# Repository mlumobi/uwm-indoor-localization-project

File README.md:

# UWB TDoA Real-time Localization

An EC601 course project to build and evaluate an indoor location system for tagged objects using ultra wideband (UWB) radio and uplink time difference of arrival (TDoA).

This is a one-person project. Mingjin Lu is responsible for hardware integration, firmware, localization software, evaluation, and documentation, with AI assistance.

**Status:** Proposal stage. This repository currently contains the project proposal and reference documents. Firmware, localization software, and measured performance results are not yet included. Accuracy, update rate, and reliability values below are proposed targets, not demonstrated capabilities.

## Five Ws and How

| Question | Project definition |
| --- | --- |
| **What** | An indoor monitoring prototype for tagged robots and vehicles, with a live 2D map, distinct tag IDs, position freshness and validity indicators, configurable safety zones, alerts for non-permitted zone entry, abnormal motion and prolonged signal loss, and recorded-movement replay. The physical prototype targets two tags and three anchors; additional tags may be simulated and clearly labeled. |
| **Who** | The primary target user is a warehouse or factory safety manager overseeing a shared workspace with vehicles, people, robots, and machinery. A robotics engineer also needs to monitor a robot without integrating with its onboard navigation software. Mingjin Lu is the sole developer, with AI assistance; user needs and interface usefulness still require interviews. |
| **Why** | Help the user see where tagged robots or vehicles are, recognize restricted-zone entries and unreliable tracking information, and review past movement. Evaluate these monitoring functions against measured ground truth and scripted scenarios; improved workplace safety and attack detection are not established outcomes. |
| **When** | The Sprint 1 two-week demo will show a labeled Python simulation, purchase and delivery progress, and the hardware implementation plan. After parts arrive, bring up the hardware, validate anchor clock correction, demonstrate one physical tag, then add the second tag and evaluate tracking and alerts. |
| **Where** | The intended application is a shared warehouse or factory workspace. Initial physical evaluation will use a controlled, surveyed indoor test area with known tag height and mapped zone boundaries; assembly and electrical checks are planned at RASTIC. Industrial deployment requires separate validation. |
| **How** | Start with simulated UWB arrival timestamps to test localization, map display, alerts, and replay. For hardware, use DWM3000 modules with XIAO ESP32C3 controllers: tags broadcast uplink blinks, three anchors record receive timestamps, and a computer corrects anchor clocks using periodic anchor-to-anchor UWB two-way exchanges, calculates TDoA positions, and applies the monitoring rules. Wi-Fi forwards records. Retain position and alert logs, compare accuracy and delay with ground truth, and use tag-to-anchor TWR as the fallback if clock correction fails its timing criteria. |

## Planned demonstration

- Two tags and three fixed anchors, each using a DWM3000 UWB module with an ESP32 or another compatible microcontroller.
- A controlled 2D test area with surveyed anchor positions and known tag height.
- Wi-Fi forwarding of timestamp records to a central computer; Bluetooth remains an option to evaluate.
- A live map with tag IDs, position age, and invalid or stale states.
- Raw measurement logs and replayable evaluation results.

Qorvo lists the DWM3000 for TWR and TDoA tag or anchor use, with a customer-supplied MCU. The module does not integrate Bluetooth, so any Bluetooth connection must come from another component. These specifications support the proposed architecture but do not establish this prototype’s performance. [Qorvo DWM3000](https://www.qorvo.com/products/p/DWM3000)

## Localization architecture

```text
Two UWB tags
    │ UWB broadcasts with tag ID and sequence number
    v
Three fixed anchors
    │ Hardware arrival timestamps and receive diagnostics
    │ Wi-Fi backhaul
    v
Central computer
    Clock correction -> frame matching -> TDoA solver -> map and logs
```

In uplink TDoA, anchors observe the same tag transmission. Differences in its arrival times correspond to differences in path lengths. Anchor clock synchronization or correction is essential; Wi-Fi or Bluetooth transports the records and does not, by itself, establish the required UWB timing basis. The proposed records therefore contain **arrival timestamps**, rather than independently measured tag-to-anchor distances. [ESP32 and DWM3000 study](https://arxiv.org/html/2403.10194v1)

**Recommended first experiment:** Verify that the selected boards and driver can produce consistent, corrected timestamps before building the full interface. A published ESP32/DWM3000 system uses two-way ranging (TWR); it provides hardware precedent but does not validate my uplink TDoA design. TWR may serve as a hardware baseline or an explicitly labeled fallback. [ESP32 and DWM3000 study](https://arxiv.org/html/2403.10194v1)

Three anchors provide two independent time differences for a known-height 2D model. This is a minimal configuration with no extra measurement redundancy; it does not guarantee a unique or well-conditioned position. A fourth anchor is a recommended improvement if resources allow. Anchor placement and obstructed radio paths must be evaluated because both affect TDoA localization quality. [Sensor placement study](https://arxiv.org/abs/2204.04508)

## Proposed evaluation targets

These targets require confirmation after user interviews and the initial timing experiment.

| Measure | Proposed criterion |
| --- | --- |
| Static horizontal accuracy | Median error ≤0.30 m and 95th-percentile error ≤0.75 m across nine surveyed test positions. |
| Valid-position ratio | At least 95% of scheduled tag transmissions produce accepted positions, reported separately for each tag. |
| Tag transmission rate | Start at 10 Hz per tag and report the achieved valid-position update rate. |
| Stale-state detection | Mark a position stale within one second of the last accepted estimate. |
| Reproducibility | A reviewer can replay retained records and reproduce the reported metrics using the documentation. |

Calibration and evaluation data should be separated. Report missed transmissions, rejected estimates, per-position errors, and obstructed-path results. Human tracking, robot control, free-height 3D localization, and industrial deployment remain outside the initial demonstration.

## Development plan

1. Interview prospective users, confirm hardware and course dates, and test a paper map.
2. Verify board communication and anchor clock correction; create a clearly labeled recorded-data demo.
3. Demonstrate one live tag end to end, then evaluate the surveyed area.
4. Add the second tag and test identity, update behavior, and failure states.
5. Publish reproducible measurements and document failed criteria and limitations.

The proposal contains five user stories with acceptance criteria, an INVEST review, thin demo slices, and ranked assumptions with tests and pivot criteria. No feasibility test results are available yet.

## Repository contents

```text
README.md
proposal/
    UWB_Project_Proposal.docx
    UWB_Project_Proposal.pdf
ref/
    DWM3000 Data Sheet.pdf
    HID-whitepaper-UWB-guide-for-decision-makers.pdf
    qorvo-getting-back-to-basics-with-ultra-wideband-uwb-white-paper.pdf
```

- [Project proposal — Word](proposal/UWB_Project_Proposal.docx)
- [Project proposal — PDF](proposal/UWB_Project_Proposal.pdf)
- [DWM3000 data sheet](ref/DWM3000%20Data%20Sheet.pdf)
- [HID UWB whitepaper](ref/HID-whitepaper-UWB-guide-for-decision-makers.pdf)
- [Qorvo — Getting Back to Basics with Ultra-Wideband (UWB)](ref/qorvo-getting-back-to-basics-with-ultra-wideband-uwb-white-paper.pdf)

The HID whitepaper is retained as a background reference; it was not used as evidence in the current proposal. Setup and execution instructions will be added when runnable software is available.

## Sources and course guide

- [EC601_Sprint1](https://docs.google.com/presentation/d/1xGqi0pRQQJJB1kcCf-J-DX_ZKf9MRdXoSHOy6zalLVk/edit?slide=id.p1#slide=id.p1) — recurring reference for this project's Sprint 1 plan. When referring to the "Sprint 1 slides" or "EC601_Sprint1," use this deck. Slide 2 lists the required plan sections, including the primary target user.
- [EC601 Defining Your Project](https://docs.google.com/presentation/d/1mjnqe2xNa9wXm628SlQiQ_eo9ZSn7dLjxyB_iZE9pWU/edit) — project definition, mission, users, stories, INVEST, thin slicing, and assumption testing.
- [Qorvo DWM3000 product information](https://www.qorvo.com/products/p/DWM3000) — component capabilities and intended applications.
- [Qorvo, Getting Back to Basics with Ultra-Wideband (UWB), May 2021](ref/qorvo-getting-back-to-basics-with-ultra-wideband-uwb-white-paper.pdf) — manufacturer white paper explaining UWB timing principles and TWR, TDoA, reverse TDoA, and PDoA topologies. Its TDoA discussion informs the planned synchronized-anchor architecture; general performance claims do not establish this prototype's accuracy, update rate, or battery life.
- [Espressif ESP32-C3 Series Datasheet](https://www.espressif.com/sites/default/files/documentation/esp32-c3_datasheet_en.pdf) — MCU radio and peripheral capabilities for the selected XIAO ESP32C3 controller; read alongside Seeed's board guide.
- [Krebs and Herter, 2024](https://arxiv.org/html/2403.10194v1) — an ESP32/DWM3000 TWR prototype and its measured limitations.
- [Zhao, Goudar, and Schoellig, 2022](https://arxiv.org/abs/2204.04508) — TDoA sensor placement and obstacle-induced measurement bias.

External technical claims should be supported by sources. Design recommendations, assumptions, and measured project results should remain distinguishable throughout development.

## AI collaboration

This one-person project is developed in collaboration with an AI agent, following the EC601 course guidelines. AI assistance is used for research, drafting, design review, and development support. The sole project owner remains responsible for verifying sources, testing implementations, and reporting results accurately.

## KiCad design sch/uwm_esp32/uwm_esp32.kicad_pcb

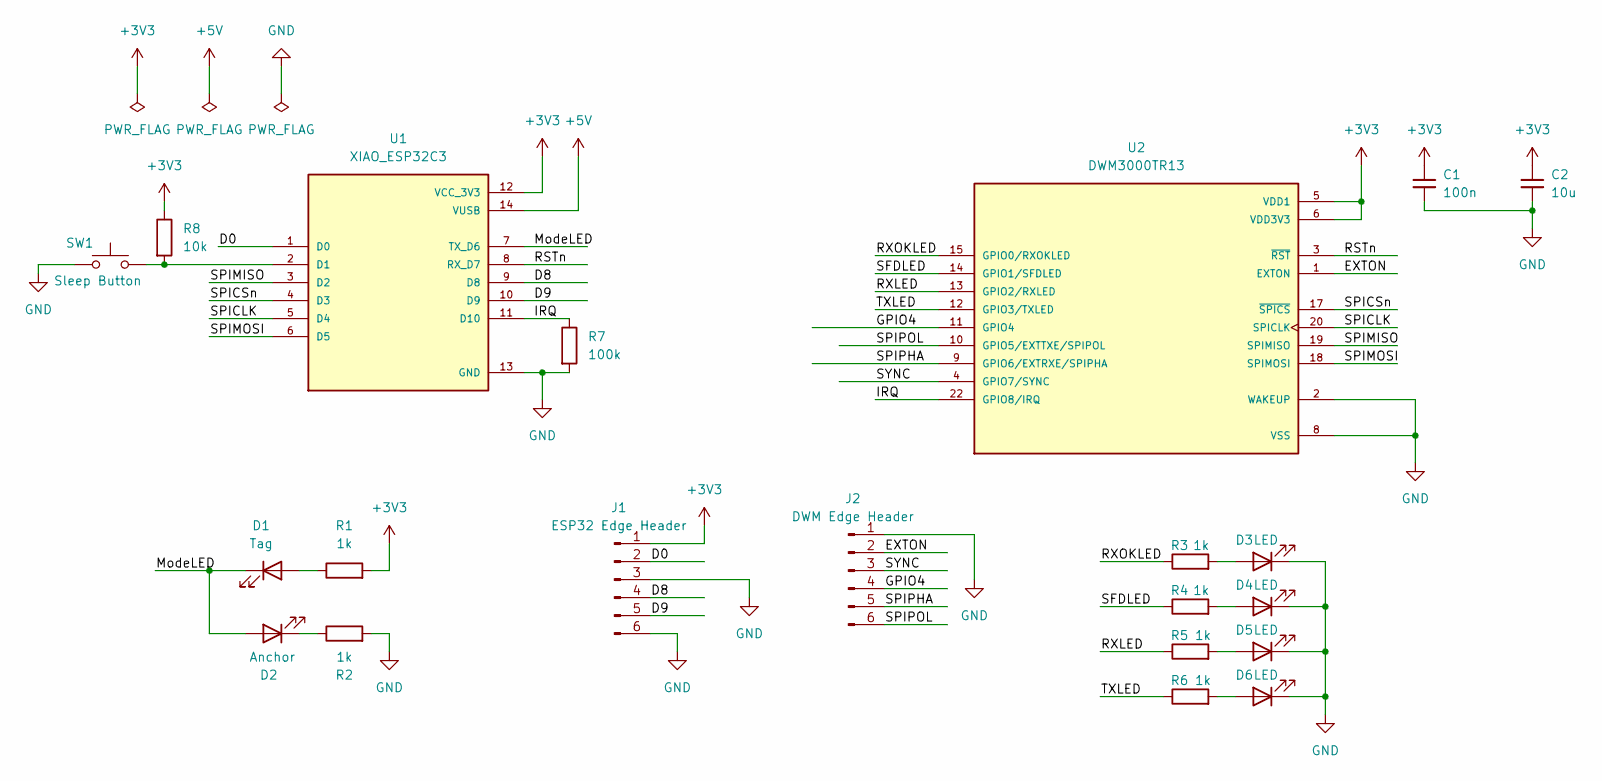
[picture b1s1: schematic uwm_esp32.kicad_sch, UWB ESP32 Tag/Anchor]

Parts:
C1: 100n; C_0805_2012Metric_Pad1.18x1.45mm_HandSolder
C2: 10u; C_0805_2012Metric_Pad1.18x1.45mm_HandSolder
D1: Tag; LED_0805_2012Metric_Pad1.15x1.40mm_HandSolder
D2: Anchor; LED_0805_2012Metric_Pad1.15x1.40mm_HandSolder
D3, D4, D5, D6: LED; LED_0805_2012Metric_Pad1.15x1.40mm_HandSolder
J1: ESP32 Edge Header; PinHeader_1x06_P2.54mm_Vertical
J2: DWM Edge Header; PinHeader_1x06_P2.54mm_Vertical
R1, R2, R3, R4, R5, R6: 1k; R_0805_2012Metric_Pad1.20x1.40mm_HandSolder
R7: 100k; R_0805_2012Metric_Pad1.20x1.40mm_HandSolder
R8: 10k; R_0805_2012Metric_Pad1.20x1.40mm_HandSolder
SW1: Sleep Button; SW_SPST_Omron_B3FS-101xP
U1: XIAO_ESP32C3; MODULE_XIAO_ESP32C3; PARTREV 23/05/2022
U2: DWM3000TR13; XCVR_DWM3000TR13; PARTREV B

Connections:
+3V3: C1.1, C2.1, J1.1, R1.2, R8.1, U1.12 (VCC_3V3), U2.5 (VDD1), U2.6 (VDD3V3), U2.7 (VDD3V3)
+5V: U1.14 (VUSB)
/D0: J1.2, U1.1 (D0)
/D8: J1.4, U1.9 (D8)
/D9: J1.5, U1.10 (D9)
/EXTON: J2.2, U2.1 (EXTON)
/GPIO4: J2.4, U2.11 (GPIO4)
/IRQ: R7.1, U1.11 (D10), U2.22 (GPIO8/IRQ)
/ModeLED: D1.1 (K), D2.2 (A), U1.7 (TX_D6)
/RSTn: U1.8 (RX_D7), U2.3 (~RST)
/RXLED: R5.1, U2.13 (GPIO2/RXLED)
/RXOKLED: R3.1, U2.15 (GPIO0/RXOKLED)
/SFDLED: R4.1, U2.14 (GPIO1/SFDLED)
/SPICLK: U1.5 (D4), U2.20 (SPICLK)
/SPICSn: U1.4 (D3), U2.17 (~SPICS)
/SPIMISO: U1.3 (D2), U2.19 (SPIMISO)
/SPIMOSI: U1.6 (D5), U2.18 (SPIMOSI)
/SPIPHA: J2.5, U2.9 (GPIO6/EXTRXE/SPIPHA)
/SPIPOL: J2.6, U2.10 (GPIO5/EXTTXE/SPIPOL)
/SYNC: J2.3, U2.4 (GPIO7/SYNC)
/TXLED: R6.1, U2.12 (GPIO3/TXLED)
GND: C1.2, C2.2, D3.1 (K), D4.1 (K), D5.1 (K), D6.1 (K), J1.3, J1.6, J2.1, R2.2, R7.2, SW1.1, U1.13 (GND), U2.2 (WAKEUP), U2.8 (VSS), U2.16 (VSS), U2.21 (VSS), U2.23 (VSS), U2.24 (VSS)
unnamed: D1.2 (A), R1.1
unnamed: D2.1 (K), R2.1
unnamed: D3.2 (A), R3.2
unnamed: D4.2 (A), R4.2
unnamed: D5.2 (A), R5.2
unnamed: D6.2 (A), R6.2
unnamed: R8.2, SW1.2, U1.2 (D1)

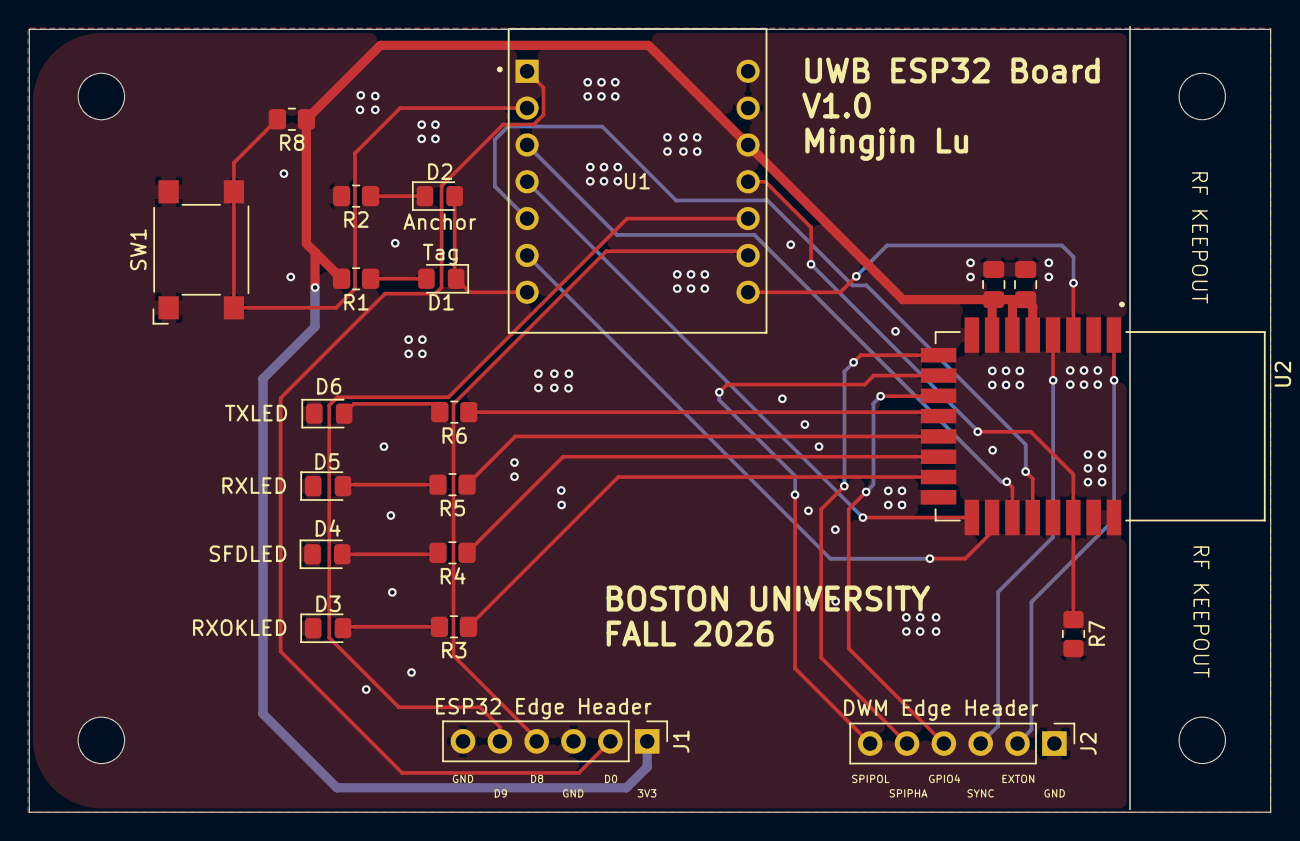
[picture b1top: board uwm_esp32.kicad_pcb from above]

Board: 2 copper layers, 85.6 x 54.0 mm, 21 parts (0 on the bottom side), 28 nets.
